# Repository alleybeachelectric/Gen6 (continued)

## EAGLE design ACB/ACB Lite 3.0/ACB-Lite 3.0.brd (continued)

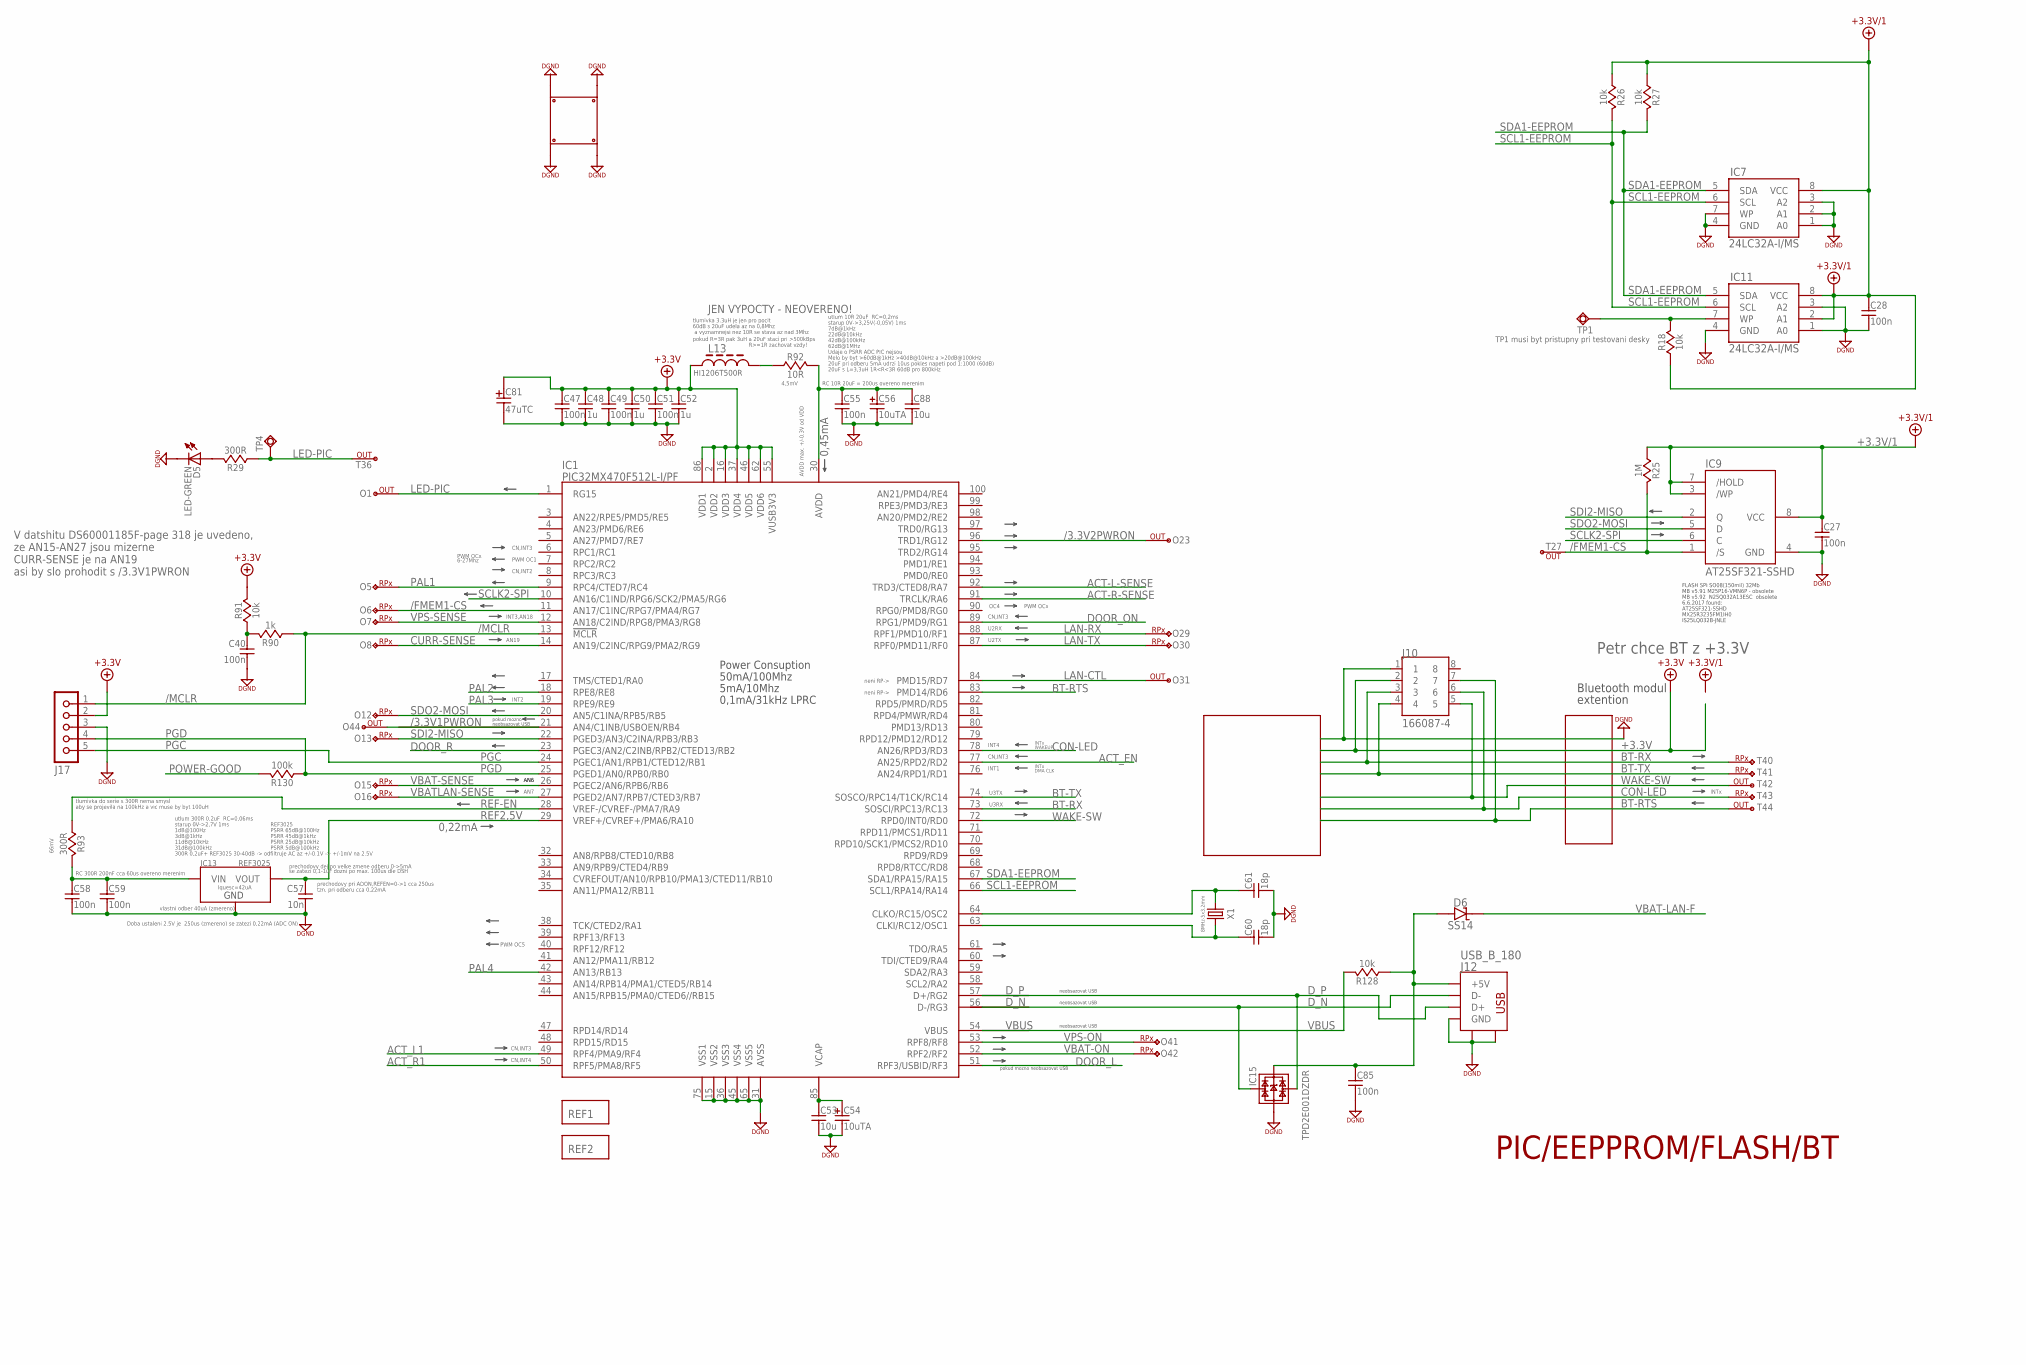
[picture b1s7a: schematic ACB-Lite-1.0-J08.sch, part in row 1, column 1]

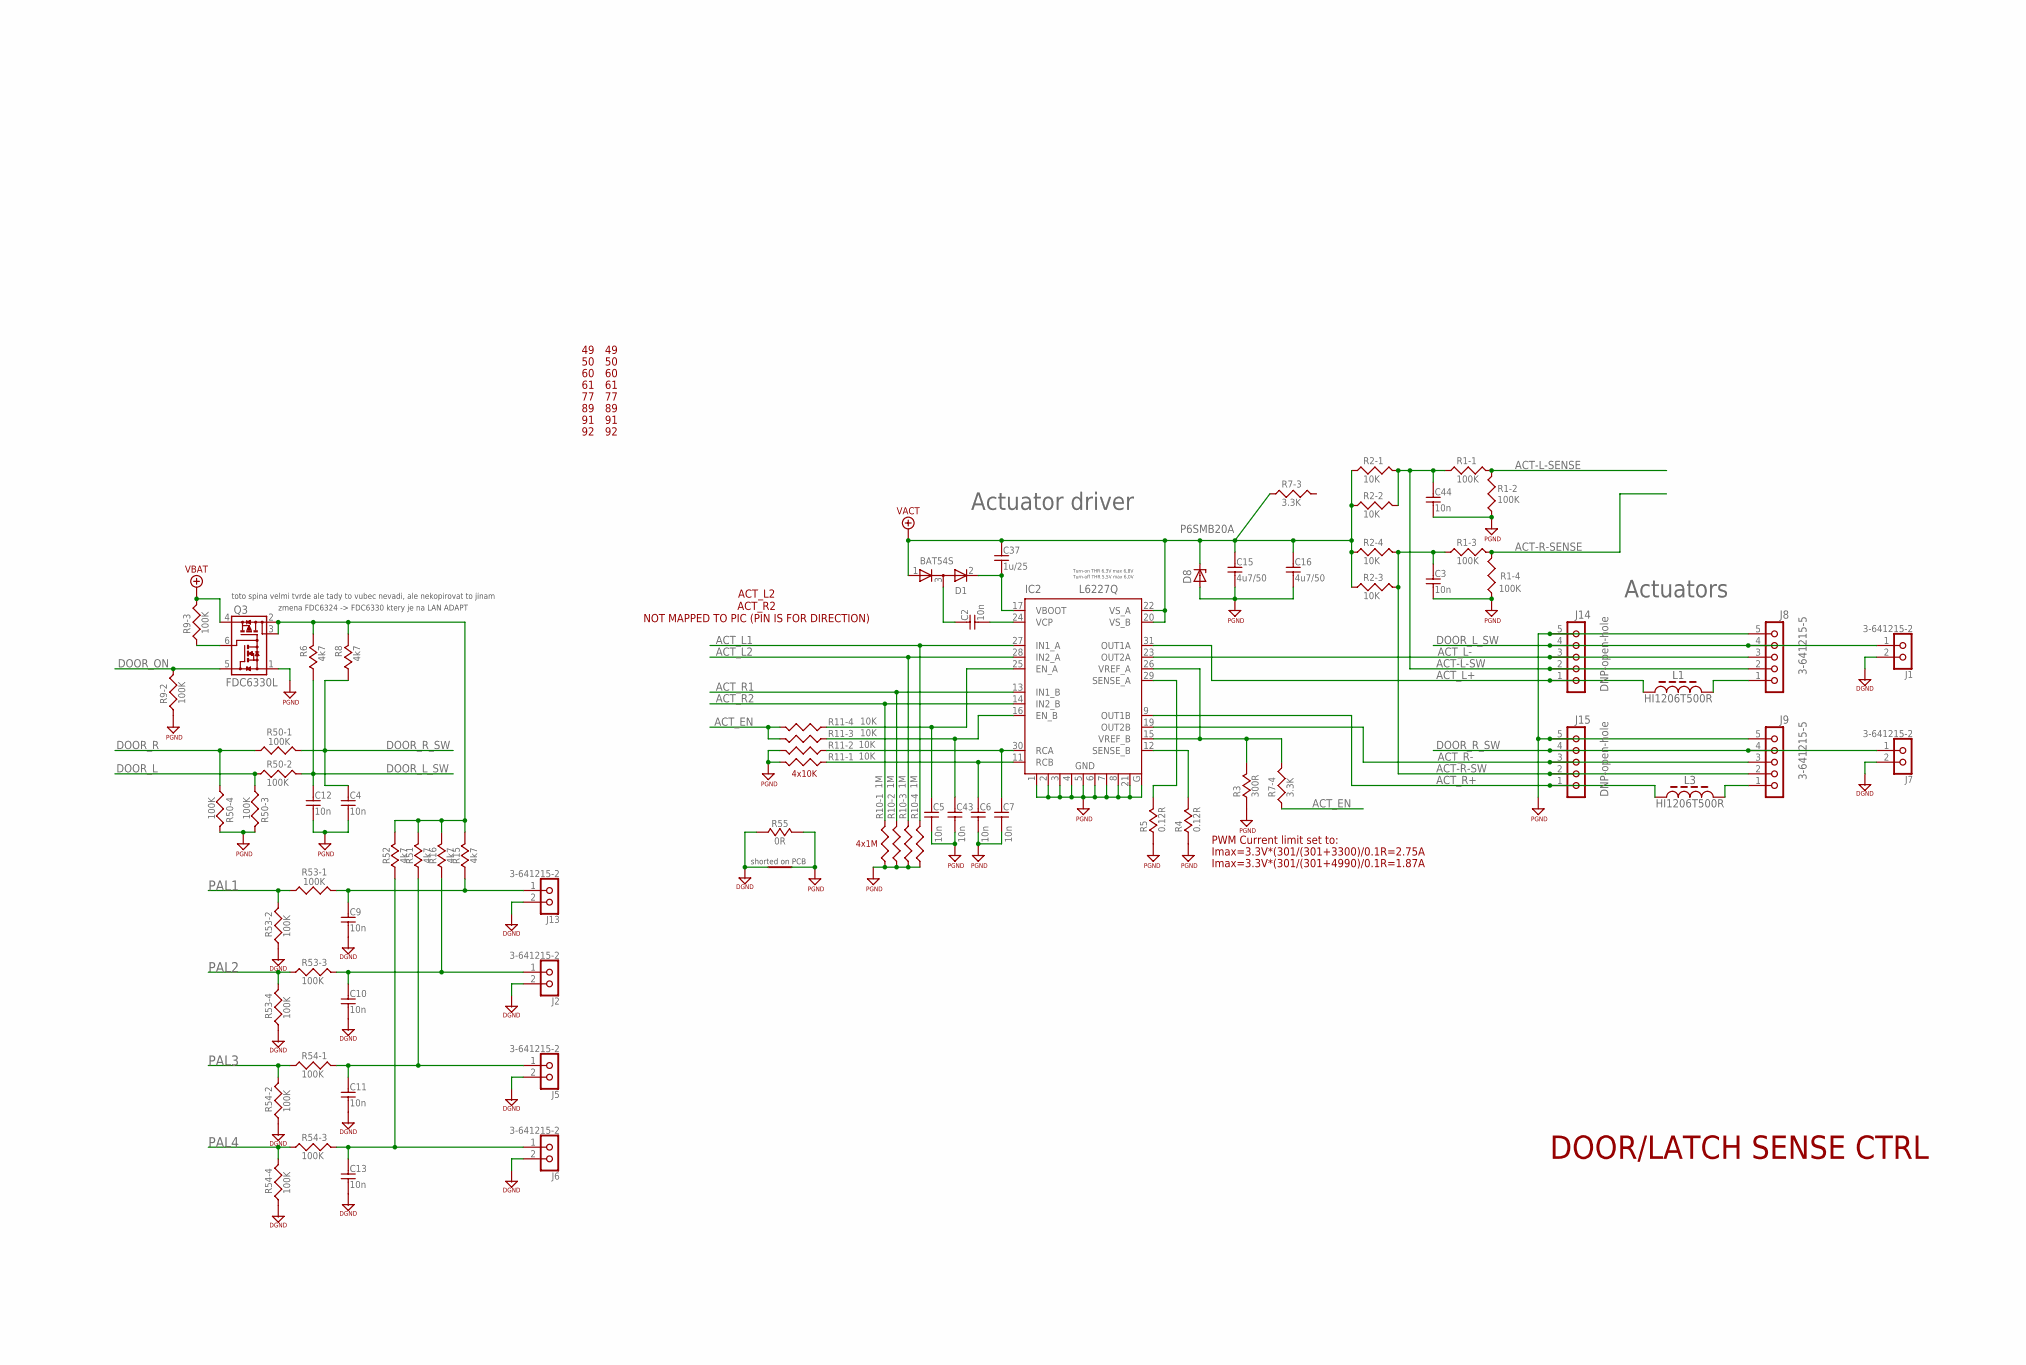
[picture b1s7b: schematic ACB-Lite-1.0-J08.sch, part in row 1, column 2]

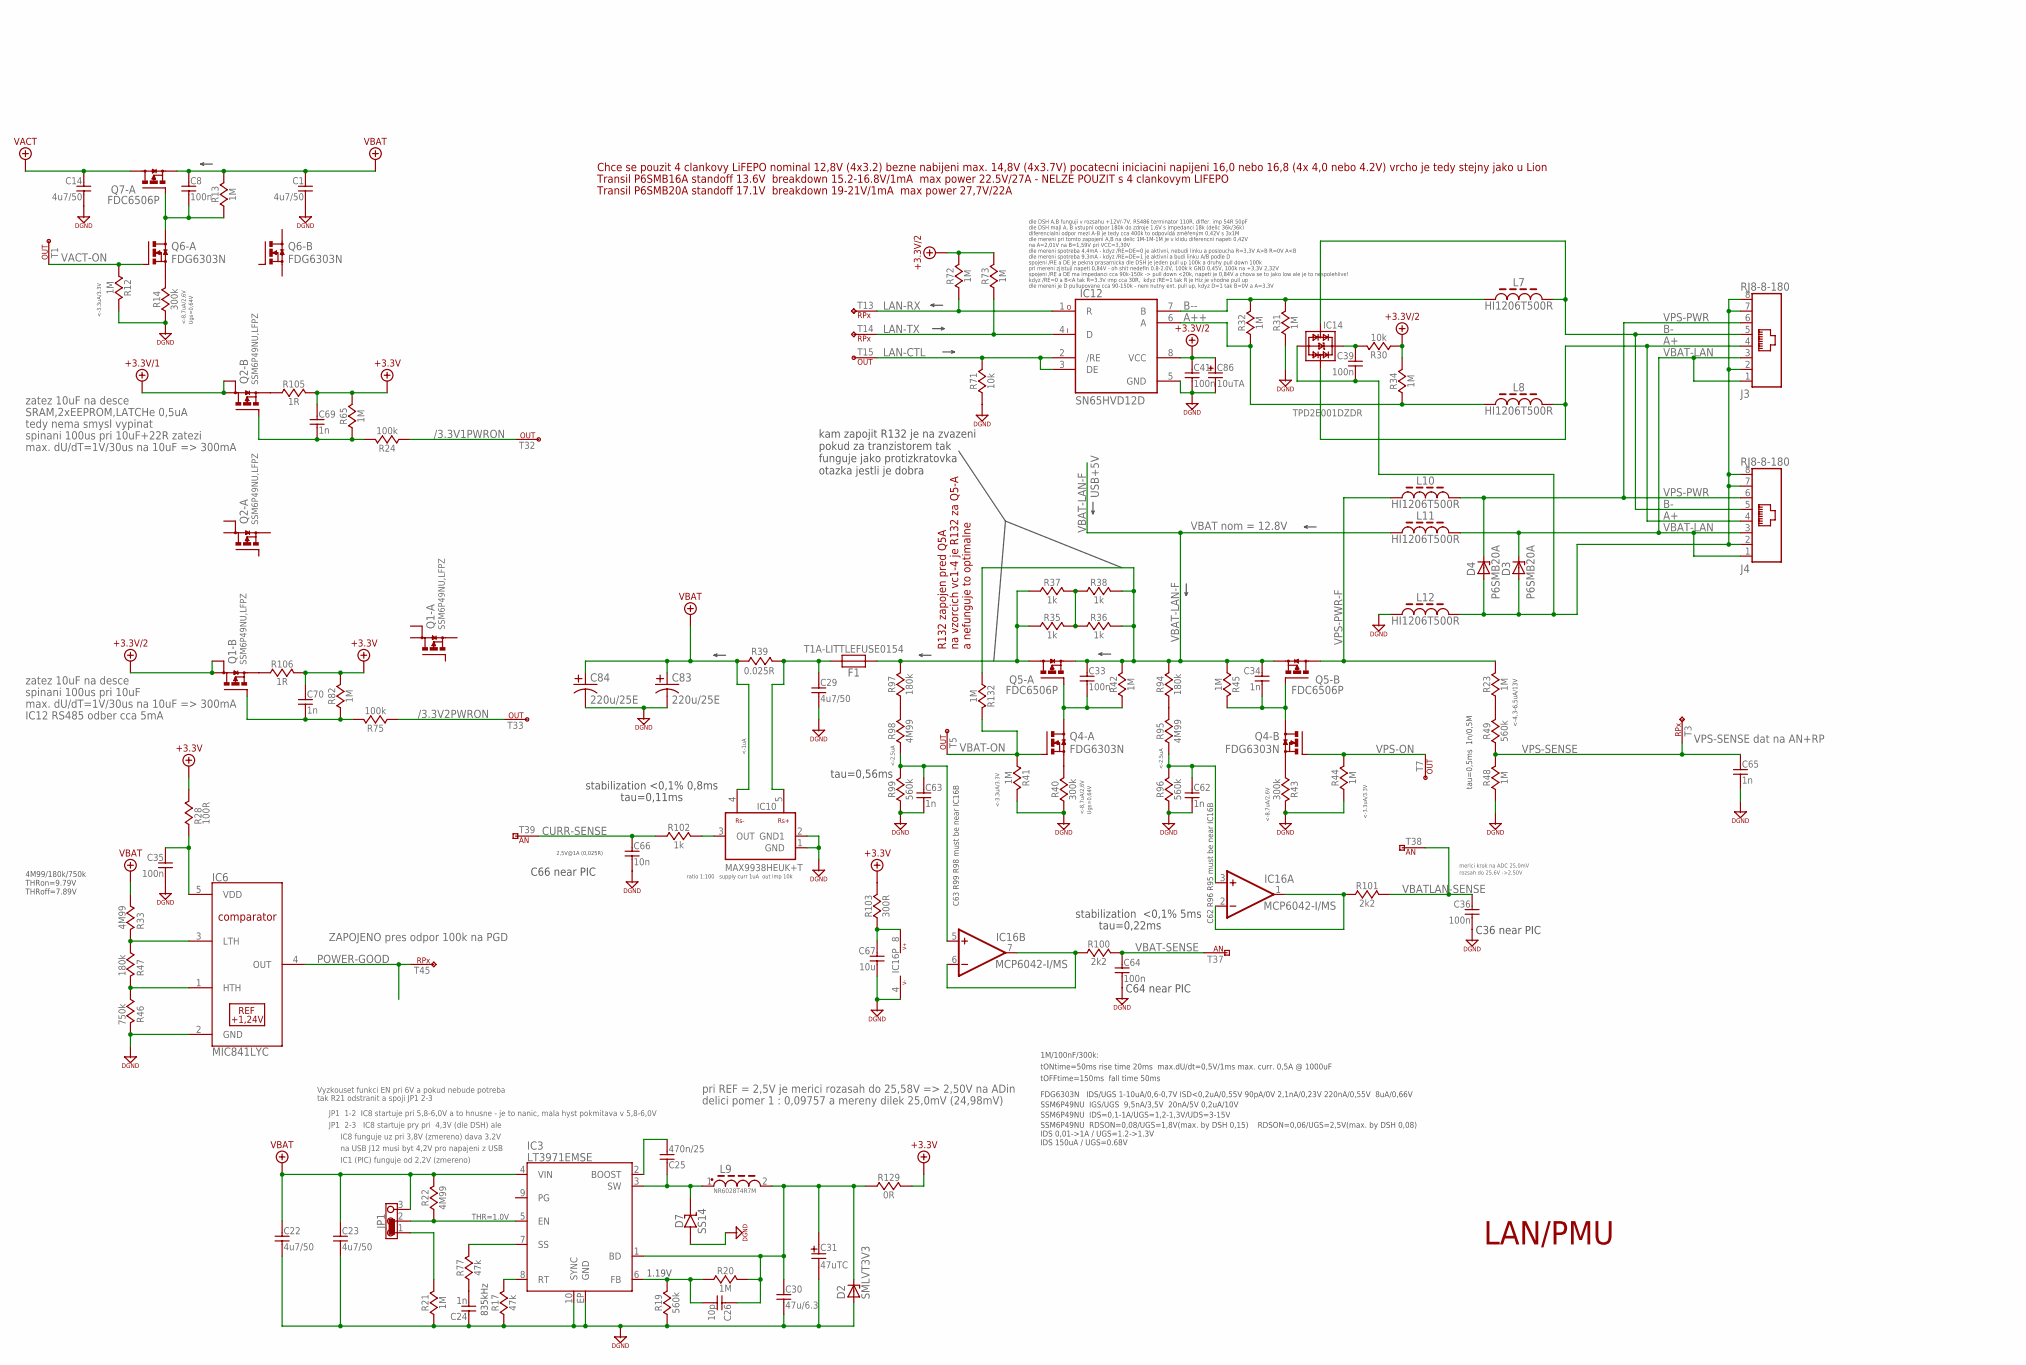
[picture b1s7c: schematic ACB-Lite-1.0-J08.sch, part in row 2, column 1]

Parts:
C1, C14, C15, C16, C22, C23, C29: 4u7/50; 1206
C2, C3, C4, C5, C6, C7, C9, C10, C11, C12, C13, C43, C44, C57, C66: 10n; 0603
C8, C27, C28, C33, C35, C36, C39, C40, C41, C47, C49, C51, C55, C58, C59, C64, C85: 100n; 0603
C24, C34, C62, C63, C65, C69, C70: 1n; 0603
C25: 470n/25; 0603
C26: 10p; 0603
C30: 47u/6.3; 1206
C31, C81: 47uTC; CT-C
C37: 1u/25; 0603
C48, C50, C52: 1u; 0603
C53, C67, C88: 10u; 0603
C54, C56, C86: 10uTA; 1206-POL-C
C60, C61: 18p; 0603
C83, C84: 220u/25E; CAP_8MM_DIA_SMT
D1: BAT54S; SOT-23
D2: SMLVT3V3; SMA
D3, D4, D8: P6SMB20A; SMB
D5: LED-GREEN; 0805-POL-D
D6, D7: SS14; SMA
F1: T1A-LITTLEFUSE0154; LITTLEFUSE0154
IC1: PIC32MX470F512L-I/PF; TQFP100_14X14_0,5MM
IC2: L6227Q; SQFP-S-5X5-32
IC3: LT3971EMSE; MSOP10EXP
IC6: MIC841LYC; SC-70-5
IC7, IC11: 24LC32A-I/MS; MSOP-08
IC9: AT25SF321-SSHD; SO-08
IC10: MAX9938HEUK+T; SOT23-5
IC12: SN65HVD12D; SO08
IC13: REF3025; SOT23
IC14, IC15: TPD2E001DZDR; SOT-143
IC16: MCP6042-I/MS; MSOP-08
J1, J2, J5, J6, J7, J13: 3-641215-2
J3, J4: RJ8-8-180
J8, J9: 3-641215-5
J10: 166087-4
J12: USB_B_180
J14, J15: DNP-open-hole; 3-641215-5
J17: DNP-open-hole; MA05-1
JP1: JP3CLOSE12
L1, L3, L7, L8, L10, L11, L12, L13: HI1206T500R; 1206
L9: NR6028T4R7M; NR6028
O1, O23, O31, O44: PIC-OUT; TEMP-PAD
O5, O6, O7, O8, O12, O13, O15, O16, O29, O30, O41, O42: PIC-RPX; TEMP-PAD
PCB1: PCB-ACB20
Q1, Q2: SSM6P49NU,LFPZ; MICRO_FET
Q3: FDC6330L; SSOT-6
Q4, Q6: FDG6303N; SC70-6
Q5, Q7: FDC6506P; SSOT-6
R1, R9, R50, R53, R54: 100K; 0603-ARRAY
R2, R11: 10K; 0603-ARRAY
R3, R29, R93, R103: 300R; 0603
R4, R5: 0.12R; 0805
R6, R8, R15, R16, R51, R52: 4k7; 0603
R7: 3.3K; 0603-ARRAY
R10: 1M; 0603-ARRAY
R12, R13, R20, R21, R23, R25, R31, R32, R34, R41, R42, R44, R45, R48, R65, R72, R73, R82, R132: 1M; 0603
R14, R40, R43: 300k; 0603
R17, R77: 47k; 0603
R18, R26, R27, R30, R71, R91, R128: 10k; 0603
R19, R49, R96, R99: 560k; 0603
R22, R33, R95, R98: 4M99; 0603
R24, R75, R130: 100k; 0603
R28: 100R; 0603
R35, R36, R37, R38: 1k; 0805
R39: 0.025R; 0805
R46: 750k; 0603
R47, R94, R97: 180k; 0603
R55, R129: 0R; 0603
R90, R102: 1k; 0603
R92: 10R; 0603
R100, R101: 2k2; 0603
R105, R106: 1R; 0805
REF1, REF2: REF
T1, T5, T7, T15, T27, T32, T33, T36, T42, T44: PIC-OUT; TEMP-PAD
T3, T13, T14, T40, T41, T43, T45: PIC-RPX; TEMP-PAD
T37, T38, T39: PIN-AN; TEMP-PAD
TP1: DNP-TestPoint; SMD_ROUND_1MM
TP4: DNP-TestPoint; TH_ROUND_14MM08MM
X1: 8MHz-5x3.2mm; 7B

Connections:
+3,3V-FILT: C35.1, IC6.5 (VDD), R28.1
+3.3V: C47.1, C48.1, C49.1, C50.1, C51.1, C52.1, C69.1, C70.1, C81.+, IC1.2 (VDD2), IC1.16 (VDD3), IC1.37 (VDD4), IC1.46 (VDD5), IC1.55 (VUSB3V3), IC1.62 (VDD6), IC1.86 (VDD1), J10.2, J17.2, L13.1, R28.2, R65.1, R82.1, R91.2, R103.2, R105.2, R106.2, R129.1; also elsewhere on the board
+3.3V/1: C27.1, C28.1, IC7.8 (VCC), IC9.3 (/WP), IC9.7 (/HOLD), IC9.8 (VCC), IC11.2 (A1), IC11.8 (VCC), Q2.3 (D), Q2.P2 (D1), R18.1, R25.2, R26.1, R27.1
+3.3V/2: C41.1, C86.+, IC12.8 (VCC), Q1.3 (D), Q1.P2 (D1), R30.2, R34.1, R72.1, R73.2
/3.3V1PWRON: IC1.21 (AN4/C1INB/USBOEN/RB4), O44.P$1, R24.2, T32.P$1
/3.3V2PWRON: IC1.96 (TRD1/RG12), O23.P$1, R75.2, T33.P$1
/FMEM1-CS: IC1.11 (AN17/C1INC/RPG7/PMA4/RG7), IC9.1 (/S), O6.P$1, R25.1, T27.P$1
/MCLR: IC1.13 (!MCLR), J17.1, R90.2
A+: IC14.3, J3.4, J4.4, L8.2
A++: IC12.6 (A), L8.1, R32.2, R34.2
ACT-L-SENSE: IC1.92 (TRD3/CTED8/RA7), R1.7 (2), R1.8 (2)
ACT-R-SENSE: IC1.91 (TRCLK/RA6), R1.5 (2), R1.6 (2)
ACT_EN: IC1.77 (AN25/RPD2/RD2), R7.4 (1), R11.5 (2), R11.6 (2)
ACT_L1: IC1.49 (RPF4/PMA9/RF4), IC2.27 (IN1_A), R10.5 (2)
ACT_L2: IC2.28 (IN2_A), R10.6 (2)
ACT_L+: IC2.31 (OUT1A), J14.1, L1.1
ACT_L-: IC2.23 (OUT2A), J8.3, J14.3
ACT_R1: IC1.50 (RPF5/PMA8/RF5), IC2.13 (IN1_B), R10.7 (2); also elsewhere on the board
ACT_R2: IC2.14 (IN2_B), R10.8 (2)
ACT_R+: IC2.9 (OUT1B), J15.1, L3.1
ACT_R-: IC2.19 (OUT2B), J9.3, J15.3
AVDD: C55.1, C56.+, C88.1, IC1.30 (AVDD), R92.2
B-: IC14.2, J3.5, J4.5, L7.2
B--: IC12.7 (B), L7.1, R31.1, R32.1
BT-RTS: IC1.83 (PMD14/RD6), J10.7, T44.P$1; also elsewhere on the board
BT-RX: IC1.73 (SOSCI/RPC13/RC13), J10.3, T40.P$1; also elsewhere on the board
BT-TX: IC1.74 (SOSCO/RPC14/T1CK/RC14), J10.4, T41.P$1; also elsewhere on the board
CON-LED: IC1.78 (AN26/RPD3/RD3), J10.6, T43.P$1; also elsewhere on the board
CURR-SENSE: C66.1, IC1.14 (AN19/C2INC/RPG9/PMA2/RG9), O8.P$1, R102.2, T39.P$1
DGND-F: C39.2, D3.A, D4.A, IC14.1, J3.2, J3.7, J3.8, J4.2, J4.7, J4.8, L12.2
DOOR_L: IC1.51 (RPF3/USBID/RF3), R50.2 (1), R50.3 (1)
DOOR_L_SW: C12.1, J1.1, J8.4, J14.4, R6.2, R50.7 (2)
DOOR_ON: IC1.89 (RPG1/PMD9/RG1), Q3.5 (Q1G), R9.7 (2)
DOOR_R: IC1.23 (PGEC3/AN2/C2INB/RPB2/CTED13/RB2), R50.1, R50.4 (1)
DOOR_R_SW: C4.1, J7.1, J9.4, J15.4, R8.2, R50.8 (2)
D_N: IC1.56 (D-/RG3), IC15.2, J12.2_D- (D-)
D_P: IC1.57 (D+/RG2), IC15.3, J12.3_D+ (D+)
GATE-Q12A: C33.2, Q4.6 (D), Q5.1 (G), R42.2
GATE-Q12A1: C8.2, Q6.6 (D), Q7.1 (G), R13.2
GATE-Q12B: C34.2, Q4.3 (D), Q5.3 (G), R45.2
LAN-CTL: IC1.84 (PMD15/RD7), IC12.2 (/RE), IC12.3 (DE), O31.P$1, R71.1, T15.P$1
LAN-RX: IC1.88 (RPF1/PMD10/RF1), IC12.1 (R), O29.P$1, R72.2, T13.P$1
LAN-TX: IC1.87 (RPF0/PMD11/RF0), IC12.4 (D), O30.P$1, R73.1, T14.P$1
LED-PIC: IC1.1 (RG15), O1.P$1, R29.1, T36.P$1, TP4.P$1
unnamed: C5.1, IC2.25 (EN_A), R11.4 (1)
unnamed: C43.1, IC2.16 (EN_B), R11.3 (1)
unnamed: C6.1, IC2.11 (RCB), R11.1
unnamed: Q6.1 (S), R14.2
unnamed: C2.2, IC2.24 (VCP)
unnamed: IC11.7 (WP), R18.2, TP1.P$1
unnamed: D5.A, R29.2
unnamed: Q4.1 (S), R40.2
unnamed: Q4.4 (S), R43.2
unnamed: C39.1, IC14.4, R30.1
unnamed: C2.1, D1.3 (KA)
unnamed: R35.2, R36.1, R37.2, R38.1
unnamed: C29.1, F1.1, IC10.5 (VIN+), R39.2
unnamed: L13.2, R92.1
unnamed: IC6.1 (HTH), R46.2, R47.1
unnamed: IC6.3 (LTH), R33.1, R47.2
unnamed: IC2.12 (SENSE_B), R4.2
unnamed: C61.1, IC1.64 (CLKO/RC15/OSC2), X1.1
unnamed: Q3.6 (Q2G), R9.3 (1)
unnamed: Q1.4 (S), R106.1
unnamed: F1.2, Q5.6 (D), R35.1, R37.1, R97.1
unnamed: C60.1, IC1.63 (CLKI/RC12/OSC1), X1.3 (2)
unnamed: IC2.29 (SENSE_A), R5.2
unnamed: C58.1, C59.1, IC13.1 (VIN), R93.2
unnamed: C37.2, D1.2 (K), IC2.17 (VBOOT)
unnamed: R94.2, R95.1
unnamed: C62.1, IC16.3 (+IN), R95.2, R96.1
unnamed: C26.2, IC3.6 (FB), R19.1, R20.2
unnamed: C24.2, R77.2
unnamed: C25.1, D7.K, IC3.3 (SW), L9.1
unnamed: IC3.8 (RT), R17.1
unnamed: IC3.7 (SS), R77.1
unnamed: IC3.5 (EN), JP1.2, R22.2
unnamed: Q2.4 (S), R105.1
unnamed: C25.2, IC3.2 (BOOST)
unnamed: R97.2, R98.1
unnamed: R23.1, R49.2
unnamed: C63.1, IC16.5 (+IN), R98.2, R99.1
unnamed: IC16.6 (-IN), IC16.7 (OUT), R100.2
unnamed: C67.1, IC16.8 (V+), R103.1
unnamed: IC16.1 (OUT), IC16.2 (-IN), R101.2
unnamed: C69.2, Q2.5 (G), R24.1, R65.2
unnamed: IC10.3 (OUT), R102.1
unnamed: C40.1, R90.1, R91.1
unnamed: C7.1, IC2.30 (RCA), R11.2 (1)
unnamed: C70.2, Q1.5 (G), R75.1, R82.2
unnamed: IC2.15 (VREF_B), IC2.26 (VREF_A), R3.2, R7.5 (2)
unnamed: C85.1, D6.A, IC15.4, J12.1_+5V (+5V), R128.1
unnamed: JP1.1, R21.1
unnamed: J8.1, L1.2
unnamed: J9.1, L3.2
unnamed: R53.1, R53.7 (2)
unnamed: R53.3 (1), R53.5 (2)
unnamed: R54.1, R54.7 (2)
unnamed: R54.3 (1), R54.5 (2)
OUT+3.3V: C26.1, C30.1, C31.+, D2.+ (C), IC3.1 (BD), L9.2, R20.1, R129.2
PGC: IC1.24 (PGEC1/AN1/RPB1/CTED12/RB1), J17.5
PGD: IC1.25 (PGED1/AN0/RPB0/RB0), J17.4, R130.2
POWER-GOOD: IC6.4 (OUT), R130.1, T45.P$1; also elsewhere on the board
REF2,5V: C57.1, IC1.29 (VREF+/CVREF+/PMA6/RA10), IC13.2 (VOUT)
REF-EN: IC1.28 (VREF-/CVREF-/PMA7/RA9), R93.1
SCL1-EEPROM: IC1.66 (SCL1/RPA14/RA14), IC7.6 (SCL), IC11.6 (SCL), R26.2
SCLK2-SPI: IC1.10 (AN16/C1IND/RPG6/SCK2/PMA5/RG6), IC9.6 (C)
SDA1-EEPROM: IC1.67 (SDA1/RPA15/RA15), IC7.5 (SDA), IC11.5 (SDA), R27.2
SDI2-MISO: IC1.22 (PGED3/AN3/C2INA/RPB3/RB3), IC9.2 (Q), O13.P$1
SDO2-MOSI: IC1.20 (AN5/C1INA/RPB5/RB5), IC9.5 (D), O12.P$1
VACT-ON: Q6.2 (G), R12.1, T1.P$1
VBAT-LAN: D3.C, J3.1, J3.3, J4.1, J4.3, L11.2
VBAT-LAN-F: C33.1, C34.1, D6.K, L11.1, Q5.2 (S), Q5.5 (S), R36.2, R38.2, R42.1, R45.1, R94.1, R132.1
VBAT-ON: IC1.52 (RPF2/RF2), O42.P$1, Q4.2 (G), R41.1, R132.2, T5.P$1
VBAT-SENSE: C64.1, IC1.26 (PGEC2/AN6/RPB6/RB6), O15.P$1, R100.1, T37.P$1
VBATLAN-SENSE: C36.1, IC1.27 (PGED2/AN7/RPB7/CTED3/RB7), O16.P$1, R101.1, T38.P$1
VBUS: IC1.54 (VBUS), R128.2
VCAP: C53.1, C54.+, IC1.85 (VCAP)
VPS-ON: IC1.53 (RPF8/RF8), O41.P$1, Q4.5 (G), R44.1, T7.P$1
VPS-PWR: D4.C, J3.6, J4.6, L10.2
VPS-PWR-F: L10.1, Q5.4 (D), R23.2
VPS-SENSE: C65.1, IC1.12 (AN18/C2IND/RPG8/PMA3/RG8), O7.P$1, R48.2, R49.1, T3.P$1
WAKE-SW: IC1.72 (RPD0/INT0/RD0), J10.5, T42.P$1; also elsewhere on the board

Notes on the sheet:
MB v5.91 M25P16-VMN6P - obsolete
MB v5.92 N25Q032A13ESC obsolete
AT25SF321-SSHD
MX25R3235FM1IH0
IS25LQ032B-JNLE
FLASH SPI SO08(150mil) 32Mb
6.6.2017 found:
Power Consuption
50mA/100Mhz
5mA/10Mhz
0,1mA/31kHz LPRC
pokud mozno
TP1 musi byt pristupny pri testovani desky
neobsazovat USB
pokud mozno neobsazovat USB
PWM OCx
6-27Mhz
INTx
DMA CLK
WAKEUP
PSRR 25dB@10kHz
PSRR 65dB@100Hz
PSRR 45dB@1kHz
PSRR 5dB@100kHz
300R 0,2uF+ REF3025 30-40dB -> odfiltruje AC az +/-0.1V -> +/-1mV na 2.5V
REF3025
prechodovy dej po velke zmene odberu 0->5mA
se zatezi 0,1-1uF dozni po max. 100us dle DSH
Iquesc=42uA
tlumivka 3.3uH je jen pro pocit
PWM OC1
INT3,AN18
AN19
CN,INT3
CN,INT2
INT2
PWM OC5
AN6
AN7
CN,INT4

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
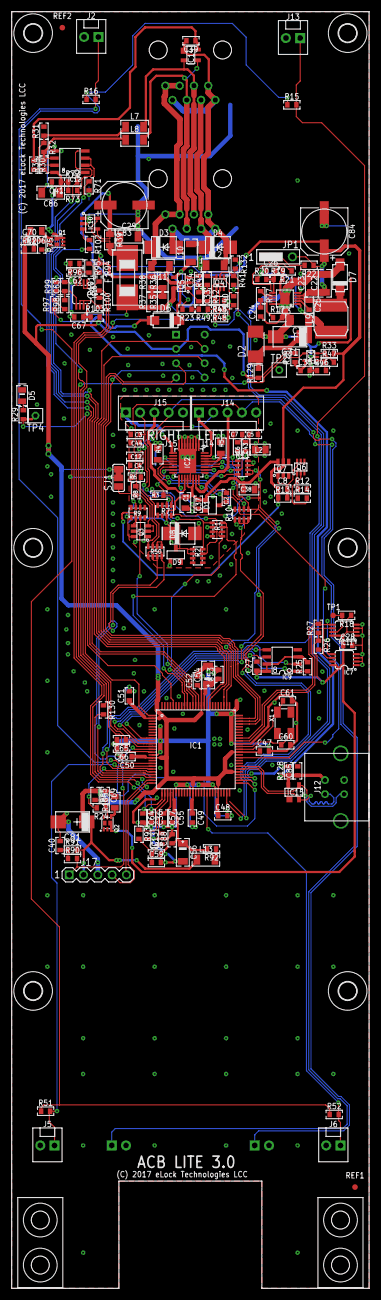
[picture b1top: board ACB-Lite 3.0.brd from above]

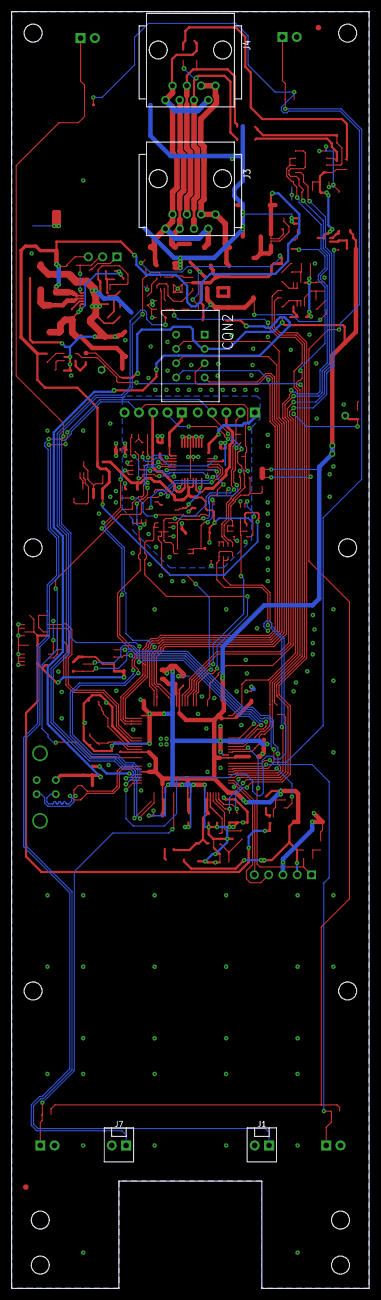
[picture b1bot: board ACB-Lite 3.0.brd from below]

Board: 2 copper layers, 63.5 x 226.8 mm, 241 parts (5 on the bottom side), 130 nets.

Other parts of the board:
H1, H2: CAM-HOLDER
H3, H4, H5, H6, H7, H8: MOUNT-HOLE3.2; 3,2
SJ1: SJ_2

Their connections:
+3.3V: SJ1.3; also elsewhere on the board

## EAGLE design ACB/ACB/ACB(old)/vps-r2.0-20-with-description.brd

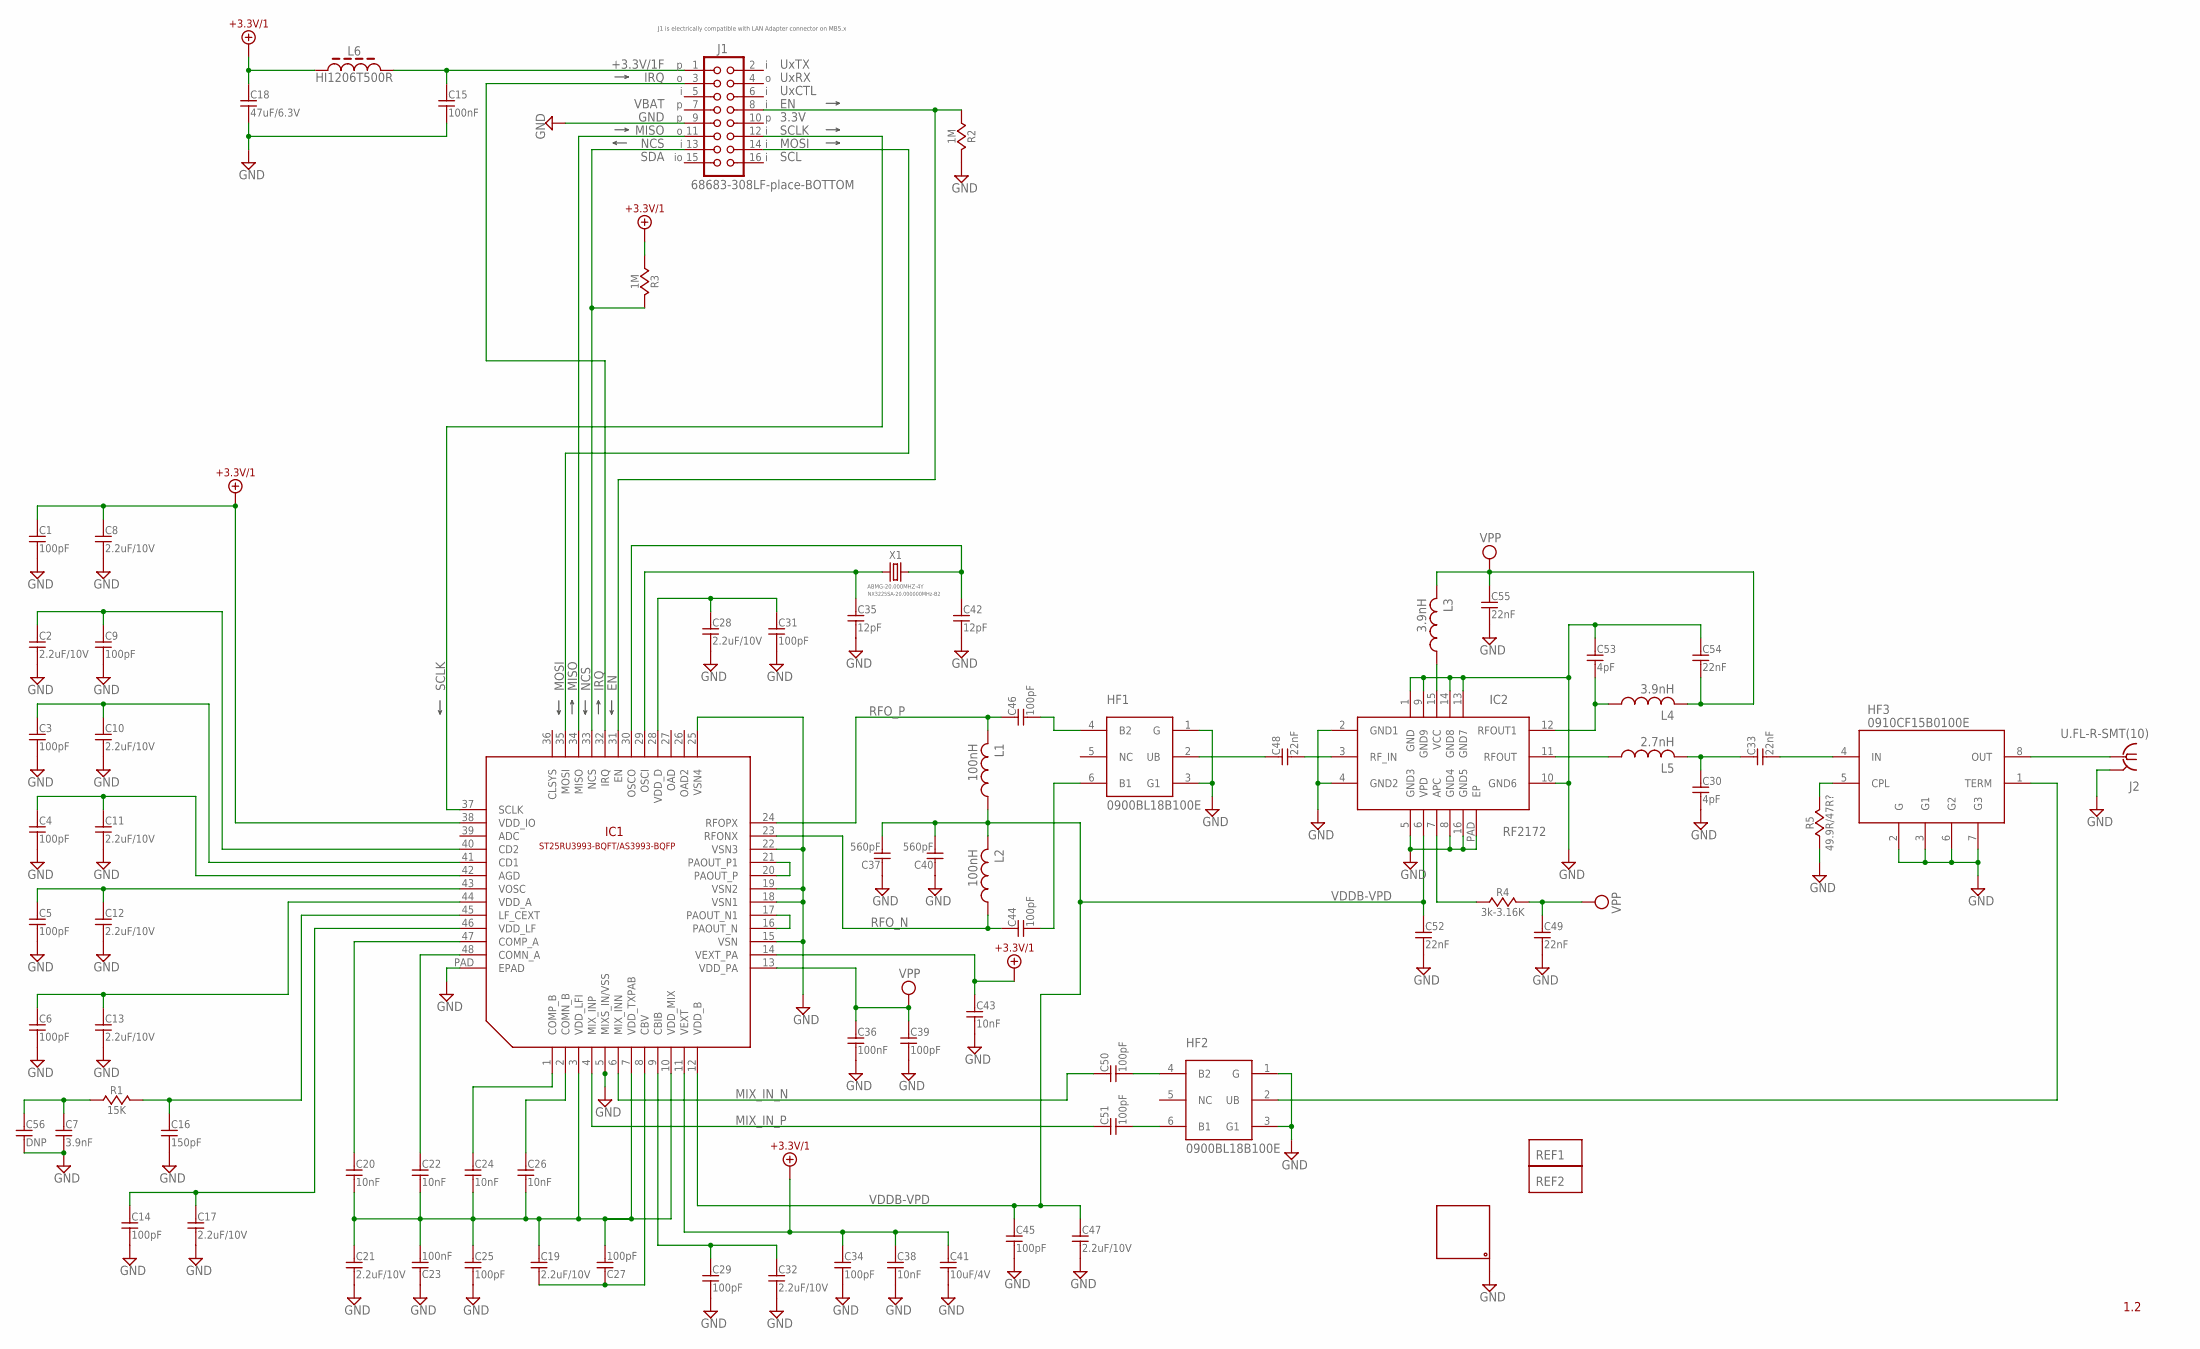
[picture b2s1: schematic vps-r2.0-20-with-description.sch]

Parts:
C1, C3, C4, C5, C6, C9, C14, C25, C27, C29, C31, C34, C39, C44, C45, C46, C50, C51: 100pF; 0603
C2, C8, C10, C11, C12, C13, C17, C19, C21, C28, C32, C47: 2.2uF/10V; 0603
C7: 3.9nF; 0603
C15, C23, C36: 100nF; 0603
C16: 150pF; 0603
C18: 47uF/6.3V; 1206
C20, C22, C24, C26, C38, C43: 10nF; 0603
C30, C53: 4pF; 0603
C33, C48, C49, C52, C54, C55: 22nF; 0603
C35, C42: 12pF; 0603
C37, C40: 560pF; 0603
C41: 10uF/4V; 0603
C56: DNP; 0603
HF1, HF2: 0900BL18B100E; JTIBALUN; MPN 0900BL18B100E; DIGIKEY 712-1023-1-ND
HF3: 0910CF15B0100E; JTICPL
IC1: ST25RU3993-BQFT/AS3993-BQFP; LFCSP_7X7_48
IC2: RF2172; QFN164X4
J1: 68683-308LF-place-BOTTOM; MA08-2
J2: U.FL-R-SMT(10); MC-921
L1, L2: 100nH; L0603
L3, L4: 3.9nH; L0603
L5: 2.7nH; L0603
L6: HI1206T500R; 1206
PCB1: PCB-VPS-1; PCB-VPS
R1: 15K; 0603
R2, R3: 1M; 0603
R4: 3k-3.16K; 0603
R5: 49.9R/47R?; 0603
REF1, REF2: REF
X1: ABMG-20.000MHZ-4Y; 7M

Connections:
+3.3V/1: C1.1, C8.1, C18.1, C34.1, C38.1, C41.1, C43.1, IC1.11 (VEXT), IC1.14 (VEXT_PA), IC1.38 (VDD_IO), L6.1, R3.1
+3.3V/1F: C15.1, J1.1, L6.2
APC: IC2.7 (APC), R4.1
EN: IC1.31 (EN), J1.8, R2.1
GND: C1.2, C2.2, C3.2, C4.2, C5.2, C6.2, C7.2, C8.2, C9.2, C10.2, C11.2, C12.2, C13.2, C14.2, C15.2, C16.2, C17.2, C18.2, C21.2, C23.1, C25.2, C28.2, C29.2, C30.2, C31.2, C32.2, C34.2, C35.2, C36.2, C37.1, C38.2, C39.2, C40.1, C41.2, C42.2, C43.2, C45.2, C47.2, C49.2, C52.2, C53.1, C54.1, C55.2, C56.2, HF1.1 (G), HF1.3 (G1), HF2.1 (G), HF2.3 (G1), HF3.2 (G), HF3.3 (G1), HF3.6 (G2), HF3.7 (G3), IC1.5 (MIXS_IN/VSS), IC1.15 (VSN), IC1.18 (VSN1), IC1.19 (VSN2), IC1.22 (VSN3), IC1.25 (VSN4), IC1.PAD (EPAD), IC2.1 (GND), IC2.2 (GND1), IC2.4 (GND2), IC2.5 (GND3), IC2.8 (GND4), IC2.9 (GND9), IC2.10 (GND6), IC2.13 (GND7), IC2.14 (GND8), IC2.16 (GND5), IC2.PAD (EP), J1.9, J2.2@1 (GND), J2.2@2 (GND), PCB1.VPS_PCB_1, R2.2, R5.1
IRQ: IC1.32 (IRQ), J1.3
MISO: IC1.34 (MISO), J1.11
MIX_IN_N: C50.1, IC1.6 (MIX_INN)
MIX_IN_P: C51.1, IC1.4 (MIX_INP)
MOSI: IC1.35 (MOSI), J1.14
unnamed: C7.1, C56.1, R1.1
unnamed: C16.1, IC1.45 (LF_CEXT), R1.2
unnamed: C20.1, IC1.47 (COMP_A)
unnamed: C22.1, IC1.48 (COMN_A)
unnamed: C24.1, IC1.1 (COMP_B)
unnamed: C26.1, IC1.2 (COMN_B)
unnamed: C6.1, C13.1, IC1.44 (VDD_A)
unnamed: C5.1, C12.1, IC1.43 (VOSC)
unnamed: C19.2, C27.1, IC1.8 (CBV)
unnamed: C4.1, C11.1, IC1.42 (AGD)
unnamed: C14.1, C17.1, IC1.46 (VDD_LF)
unnamed: C3.1, C10.1, IC1.41 (CD1)
unnamed: C2.1, C9.1, IC1.40 (CD2)
unnamed: C51.2, HF2.6 (B1)
unnamed: C29.1, C32.1, IC1.9 (CBIB)
unnamed: C35.1, IC1.29 (OSCI), X1.1
unnamed: C42.1, IC1.30 (OSCO), X1.3 (2)
unnamed: IC1.20 (PAOUT_P), IC1.21 (PAOUT_P1)
unnamed: IC1.16 (PAOUT_N), IC1.17 (PAOUT_N1)
unnamed: C30.1, C33.1, L5.2
unnamed: C33.2, HF3.4 (IN)
unnamed: C46.2, HF1.4 (B2)
unnamed: HF3.5 (CPL), R5.2
unnamed: C44.2, HF1.6 (B1)
unnamed: C48.1, HF1.2 (UB)
unnamed: HF2.2 (UB), HF3.1 (TERM)
unnamed: HF3.8 (OUT), J2.1
unnamed: C28.1, C31.1, IC1.28 (VDD_D)
unnamed: C50.2, HF2.4 (B2)
NCS: IC1.33 (NCS), J1.13, R3.2
RFIN: C48.2, IC2.3 (RF_IN)
RFOUT: IC2.11 (RFOUT), L5.1
RFOUT1: C53.2, IC2.12 (RFOUT1), L4.1
RFO_N: C44.1, IC1.23 (RFONX), L2.1
RFO_P: C46.1, IC1.24 (RFOPX), L1.2
SCLK: IC1.37 (SCLK), J1.12
VDD-FLI-MIX-TXPAB: C19.1, C20.2, C21.1, C22.2, C23.2, C24.2, C25.1, C26.2, C27.2, IC1.3 (VDD_LFI), IC1.7 (VDD_TXPAB), IC1.10 (VDD_MIX)
VDDB-VPD: C37.2, C40.2, C45.1, C47.1, C52.1, IC1.12 (VDD_B), IC2.6 (VPD), L1.1, L2.2
VPP: C36.1, C39.1, C49.1, C54.2, C55.1, IC1.13 (VDD_PA), L3.2, L4.2, R4.2
VPP3,9NH: IC2.15 (VCC), L3.1

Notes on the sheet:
1.2
J1 is electrically compatible with LAN Adapter connector on MB5.x
SCL
SDA
VBAT
UxTX
UxRX
3.3V
UxCTL
NX3225SA-20.000000MHz-B2

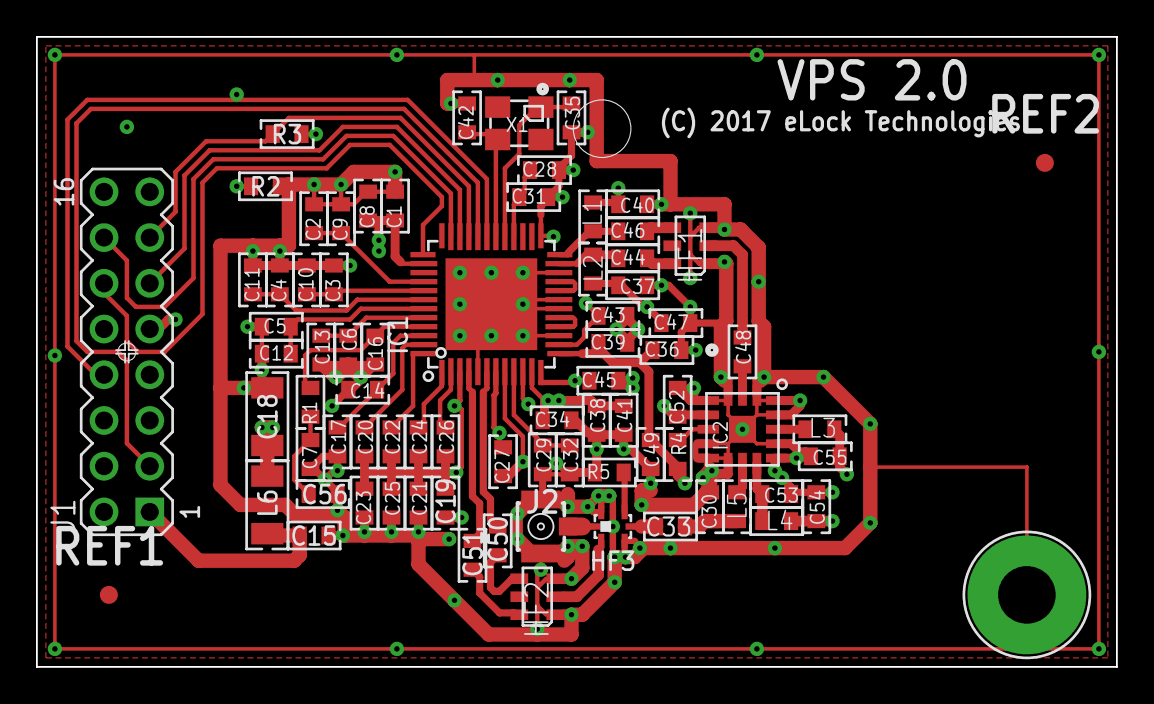
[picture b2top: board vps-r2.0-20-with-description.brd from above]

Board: 4 copper layers, 60.0 x 35.0 mm, 78 parts (0 on the bottom side), 50 nets.

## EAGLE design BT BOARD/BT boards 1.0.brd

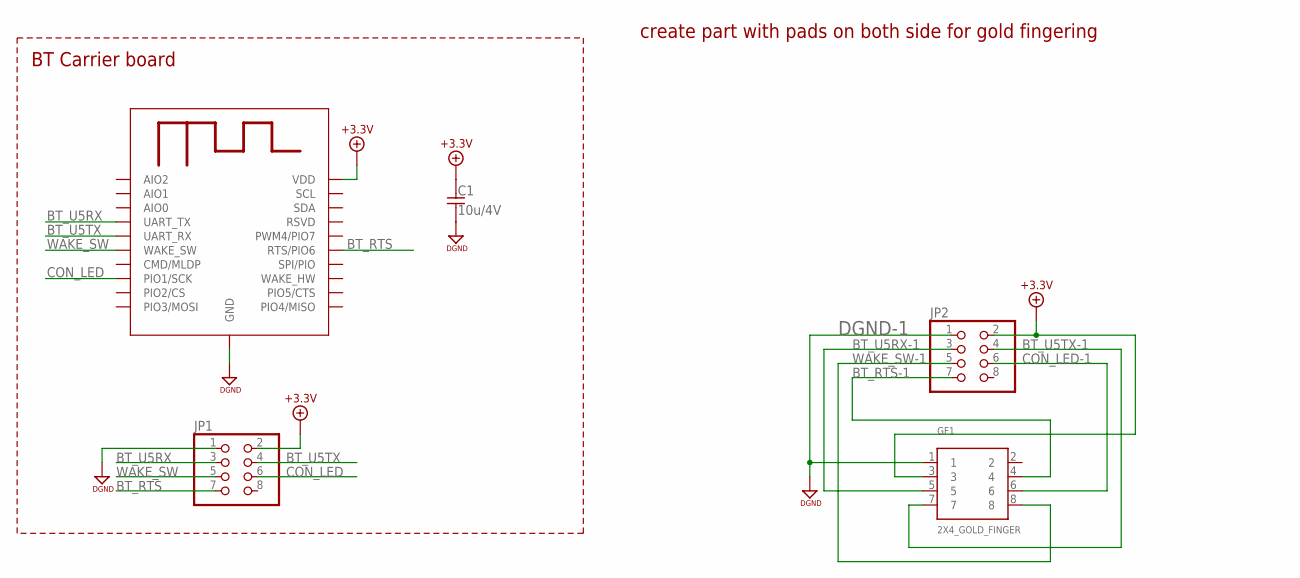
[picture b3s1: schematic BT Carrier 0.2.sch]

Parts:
C1: 10u/4V; 0603
GF1: 2X4_GOLD_FINGER
JP1, JP2: PINHD-2X4; 2X04
M1: RN4020; BT_MODULE

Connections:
+3.3V: C1.1, JP1.2, M1.23 (VDD)
+3.3V-1: GF1.3, JP2.2
BT_RTS: JP1.7, M1.18 (RTS/PIO6)
BT_RTS-1: GF1.4, JP2.7
BT_U5RX: JP1.3, M1.5 (UART_TX)
BT_U5RX-1: GF1.5, JP2.3
BT_U5TX: JP1.4, M1.6 (UART_RX)
BT_U5TX-1: GF1.7, JP2.4
CON_LED: JP1.6, M1.10 (PIO1/SCK)
CON_LED-1: GF1.6, JP2.6
DGND: C1.2, JP1.1, M1.1 (GND), M1.9 (GND), M1.9-1 (GND), M1.16 (GND), M1.16-1 (GND), M1.24 (GND)
DGND-1: GF1.1, JP2.1
WAKE_SW: JP1.5, M1.7 (WAKE_SW)
WAKE_SW-1: GF1.8, JP2.5

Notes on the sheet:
BT Carrier board
create part with pads on both side for gold fingering

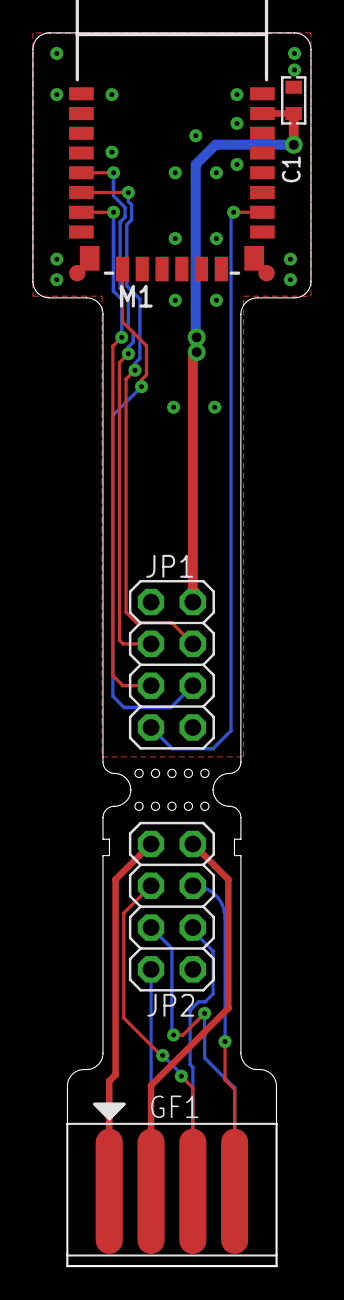
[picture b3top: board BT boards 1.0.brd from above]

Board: 2 copper layers, 16.9 x 75.0 mm, 5 parts (0 on the bottom side), 14 nets.
